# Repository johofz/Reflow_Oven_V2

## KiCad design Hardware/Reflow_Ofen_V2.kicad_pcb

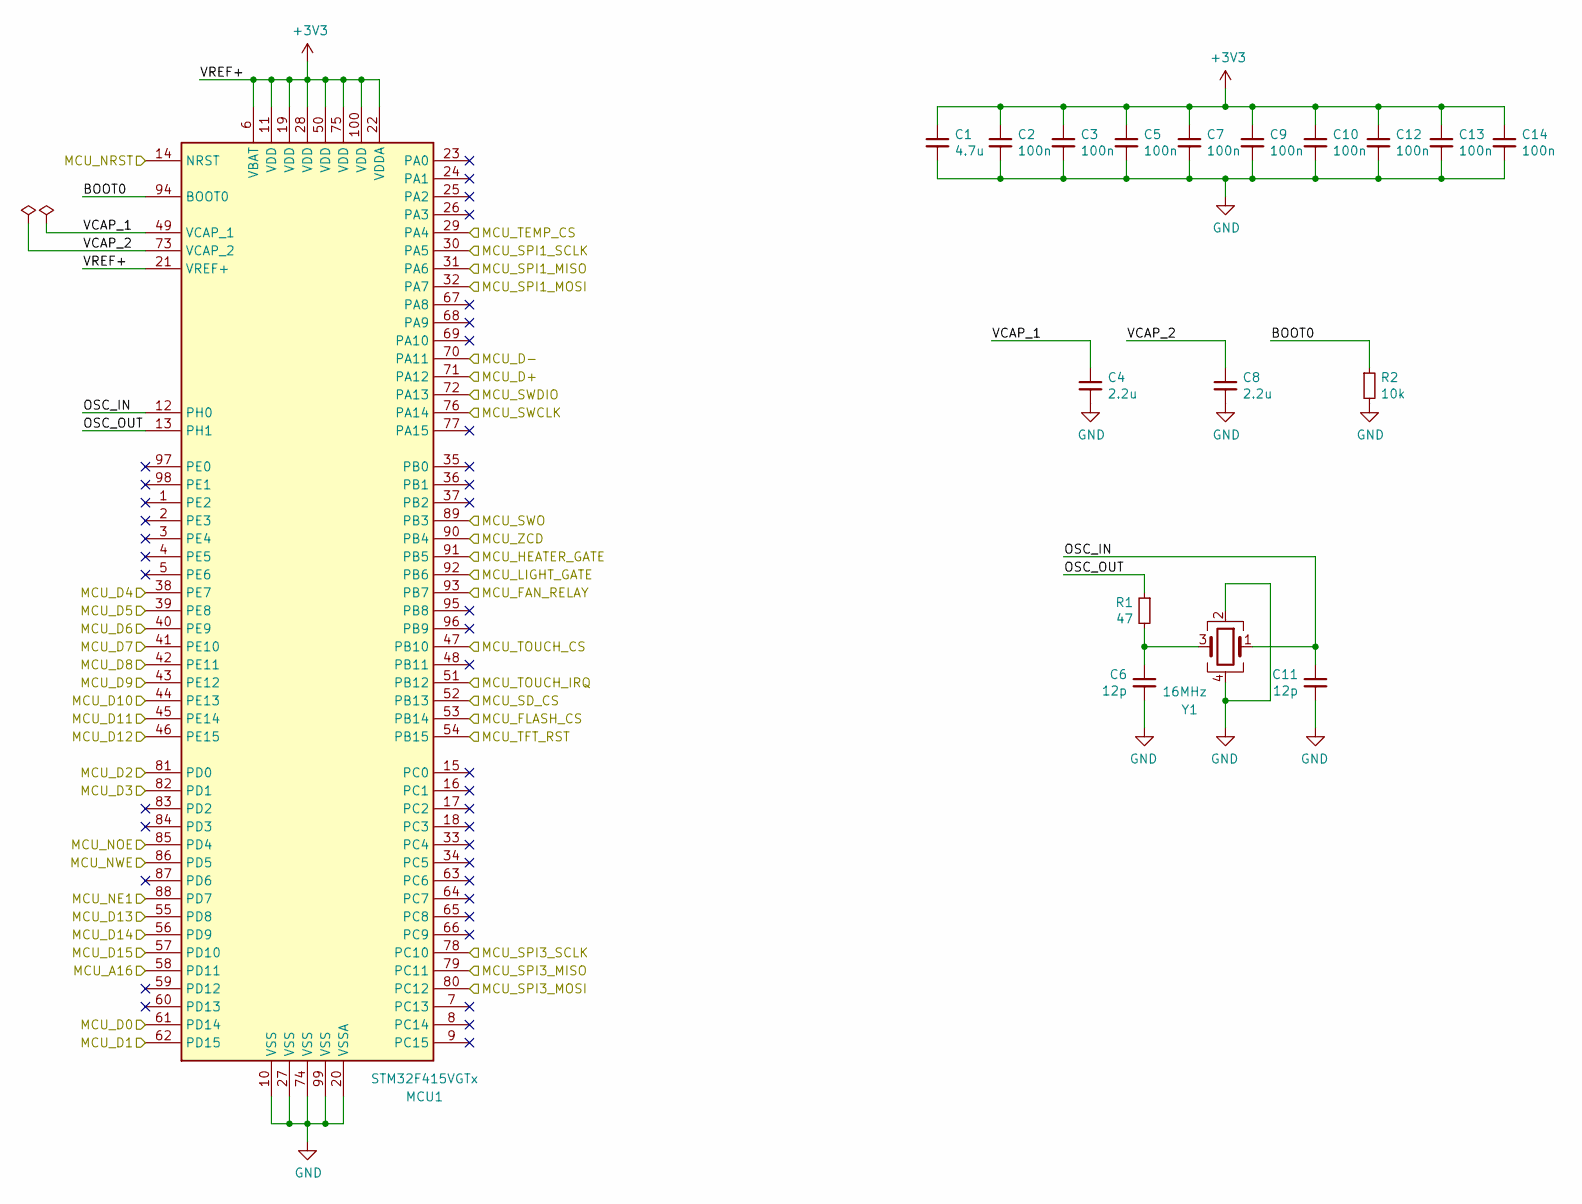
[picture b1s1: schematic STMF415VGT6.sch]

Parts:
C1: 4.7u; C_0603_1608Metric; LCSC C19666
C2, C3, C5, C7, C9, C10, C12, C13, C14: 100n; C_0402_1005Metric; LCSC C1525
C4, C8: 2.2u; C_0603_1608Metric; LCSC C23630
C6, C11: 12p; C_0402_1005Metric; LCSC C1547
MCU1: STM32F415VGTx; LQFP-100_14x14mm_P0.5mm; LCSC C118210
R1: 47; R_0402_1005Metric; LCSC C25118
R2: 10k; R_0402_1005Metric; LCSC C25744
Y1: 16MHz; Crystal_SMD_3225-4Pin_3.2x2.5mm; LCSC C13738

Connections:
/Connectors/CONN_D+: MCU1.71 (PA12); also elsewhere on the board
/Connectors/CONN_D-: MCU1.70 (PA11); also elsewhere on the board
/Connectors/CONN_NRST: MCU1.14 (NRST); also elsewhere on the board
/Connectors/CONN_SWCLK: MCU1.76 (PA14); also elsewhere on the board
/Connectors/CONN_SWDIO: MCU1.72 (PA13); also elsewhere on the board
/Connectors/CONN_SWO: MCU1.89 (PB3); also elsewhere on the board
/FLASH_CS: MCU1.53 (PB14); also elsewhere on the board
/Power-Control/FAN_GATE: MCU1.93 (PB7); also elsewhere on the board
/Power-Control/HEATER_GATE: MCU1.91 (PB5); also elsewhere on the board
/Power-Control/LIGHT_GATE: MCU1.92 (PB6); also elsewhere on the board
/SD_CS: MCU1.52 (PB13); also elsewhere on the board
/SPI3_MISO: MCU1.79 (PC11); also elsewhere on the board
/SPI3_MOSI: MCU1.80 (PC12); also elsewhere on the board
/SPI3_SCLK: MCU1.78 (PC10); also elsewhere on the board
/STMF415VGT6/BOOT0: MCU1.94 (BOOT0), R2.1
/STMF415VGT6/MCU_A16: MCU1.58 (PD11); also elsewhere on the board
/STMF415VGT6/MCU_D0: MCU1.61 (PD14); also elsewhere on the board
/STMF415VGT6/MCU_D1: MCU1.62 (PD15); also elsewhere on the board
/STMF415VGT6/MCU_D2: MCU1.81 (PD0); also elsewhere on the board
/STMF415VGT6/MCU_D3: MCU1.82 (PD1); also elsewhere on the board
/STMF415VGT6/MCU_D4: MCU1.38 (PE7); also elsewhere on the board
/STMF415VGT6/MCU_D5: MCU1.39 (PE8); also elsewhere on the board
/STMF415VGT6/MCU_D6: MCU1.40 (PE9); also elsewhere on the board
/STMF415VGT6/MCU_D7: MCU1.41 (PE10); also elsewhere on the board
/STMF415VGT6/MCU_D8: MCU1.42 (PE11); also elsewhere on the board
/STMF415VGT6/MCU_D9: MCU1.43 (PE12); also elsewhere on the board
/STMF415VGT6/MCU_D10: MCU1.44 (PE13); also elsewhere on the board
/STMF415VGT6/MCU_D11: MCU1.45 (PE14); also elsewhere on the board
/STMF415VGT6/MCU_D12: MCU1.46 (PE15); also elsewhere on the board
/STMF415VGT6/MCU_D13: MCU1.55 (PD8); also elsewhere on the board
/STMF415VGT6/MCU_D14: MCU1.56 (PD9); also elsewhere on the board
/STMF415VGT6/MCU_D15: MCU1.57 (PD10); also elsewhere on the board
/STMF415VGT6/MCU_NE1: MCU1.88 (PD7); also elsewhere on the board
/STMF415VGT6/MCU_NOE: MCU1.85 (PD4); also elsewhere on the board
/STMF415VGT6/MCU_NWE: MCU1.86 (PD5); also elsewhere on the board
/STMF415VGT6/MCU_SPI1_MISO: MCU1.31 (PA6); also elsewhere on the board
/STMF415VGT6/MCU_SPI1_SCLK: MCU1.30 (PA5); also elsewhere on the board
/STMF415VGT6/MCU_TEMP_CS: MCU1.29 (PA4); also elsewhere on the board
/STMF415VGT6/MCU_TFT_RST: MCU1.54 (PB15); also elsewhere on the board
/STMF415VGT6/MCU_ZCD: MCU1.90 (PB4); also elsewhere on the board
/STMF415VGT6/OSC_IN: C11.1, MCU1.12 (PH0), Y1.1
/STMF415VGT6/OSC_OUT: MCU1.13 (PH1), R1.1
/STMF415VGT6/VCAP_1: C4.1, MCU1.49 (VCAP_1)
/STMF415VGT6/VCAP_2: C8.1, MCU1.73 (VCAP_2)
/TOUCH_CS: MCU1.47 (PB10); also elsewhere on the board
/TOUCH_IRQ: MCU1.51 (PB12); also elsewhere on the board
GND: C1.2, C2.2, C3.2, C4.2, C5.2, C6.2, C7.2, C8.2, C9.2, C10.2, C11.2, C12.2, C13.2, C14.2, MCU1.10 (VSS), MCU1.20 (VSSA), MCU1.27 (VSS), MCU1.74 (VSS), MCU1.99 (VSS), R2.2, Y1.2, Y1.4; also elsewhere on the board
unnamed: C6.1, R1.2, Y1.3

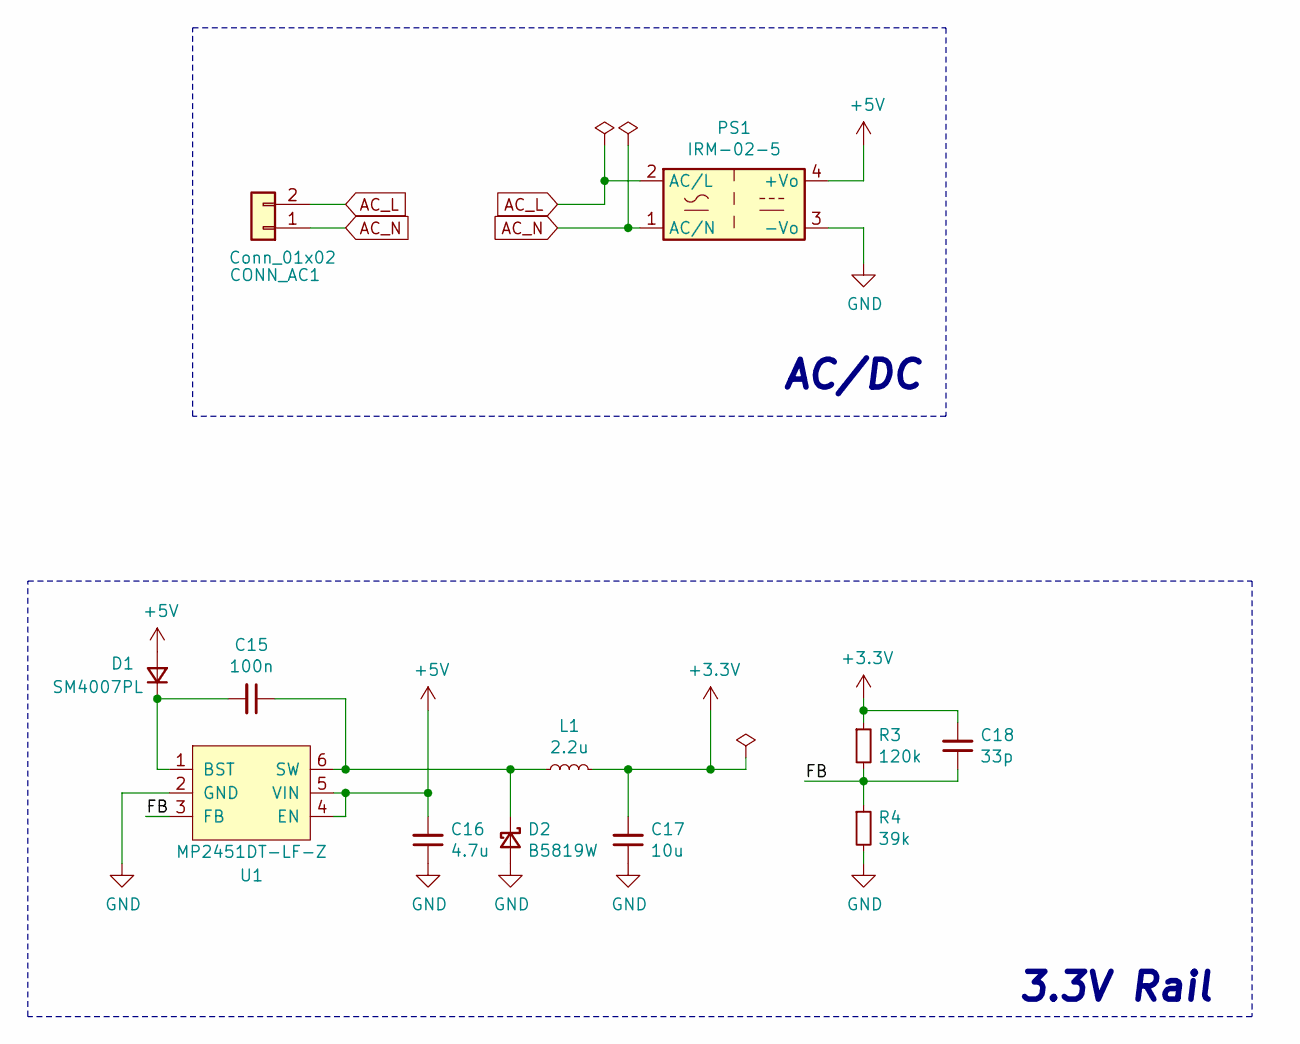
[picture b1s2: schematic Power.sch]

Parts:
C15: 100n; C_0402_1005Metric; LCSC C1525
C16: 4.7u; C_0805_2012Metric; LCSC C1779
C17: 10u; C_0805_2012Metric; LCSC C15850
C18: 33p; C_0603_1608Metric; LCSC C1663
CONN_AC1: Conn_01x02; TerminalBlock_Wuerth_691311400102_P7.62mm; LCSC C8422
D1: SM4007PL; D_SOD-123F; LCSC C64898
D2: B5819W; D_SOD-123; LCSC C8598
L1: 2.2u; L_Sunlord_MWSA0518_5.4x5.2mm; LCSC C408345
PS1: IRM-02-5; Converter_ACDC_MeanWell_IRM-02-xx_THT
R3: 120k; R_0805_2012Metric; LCSC C17436
R4: 39k; R_0805_2012Metric; LCSC C25826
U1: MP2451DT-LF-Z; TSOT-23-6; LCSC C85285

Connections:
+5V: C16.2, D1.2 (A), PS1.4 (+Vo), U1.4 (EN), U1.5 (VIN); also elsewhere on the board
/Power/FB: C18.1, R3.2, R4.1, U1.3 (FB)
AC_L: CONN_AC1.2, PS1.2 (AC/L); also elsewhere on the board
AC_N: CONN_AC1.1, PS1.1 (AC/N); also elsewhere on the board
GND: C16.1, C17.1, D2.2 (A), PS1.3 (-Vo), R4.2, U1.2 (GND); also elsewhere on the board
unnamed: C15.1, D2.1 (K), L1.1, U1.6 (SW)
unnamed: C15.2, D1.1 (K), U1.1 (BST)

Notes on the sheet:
3.3V Rail
AC/DC

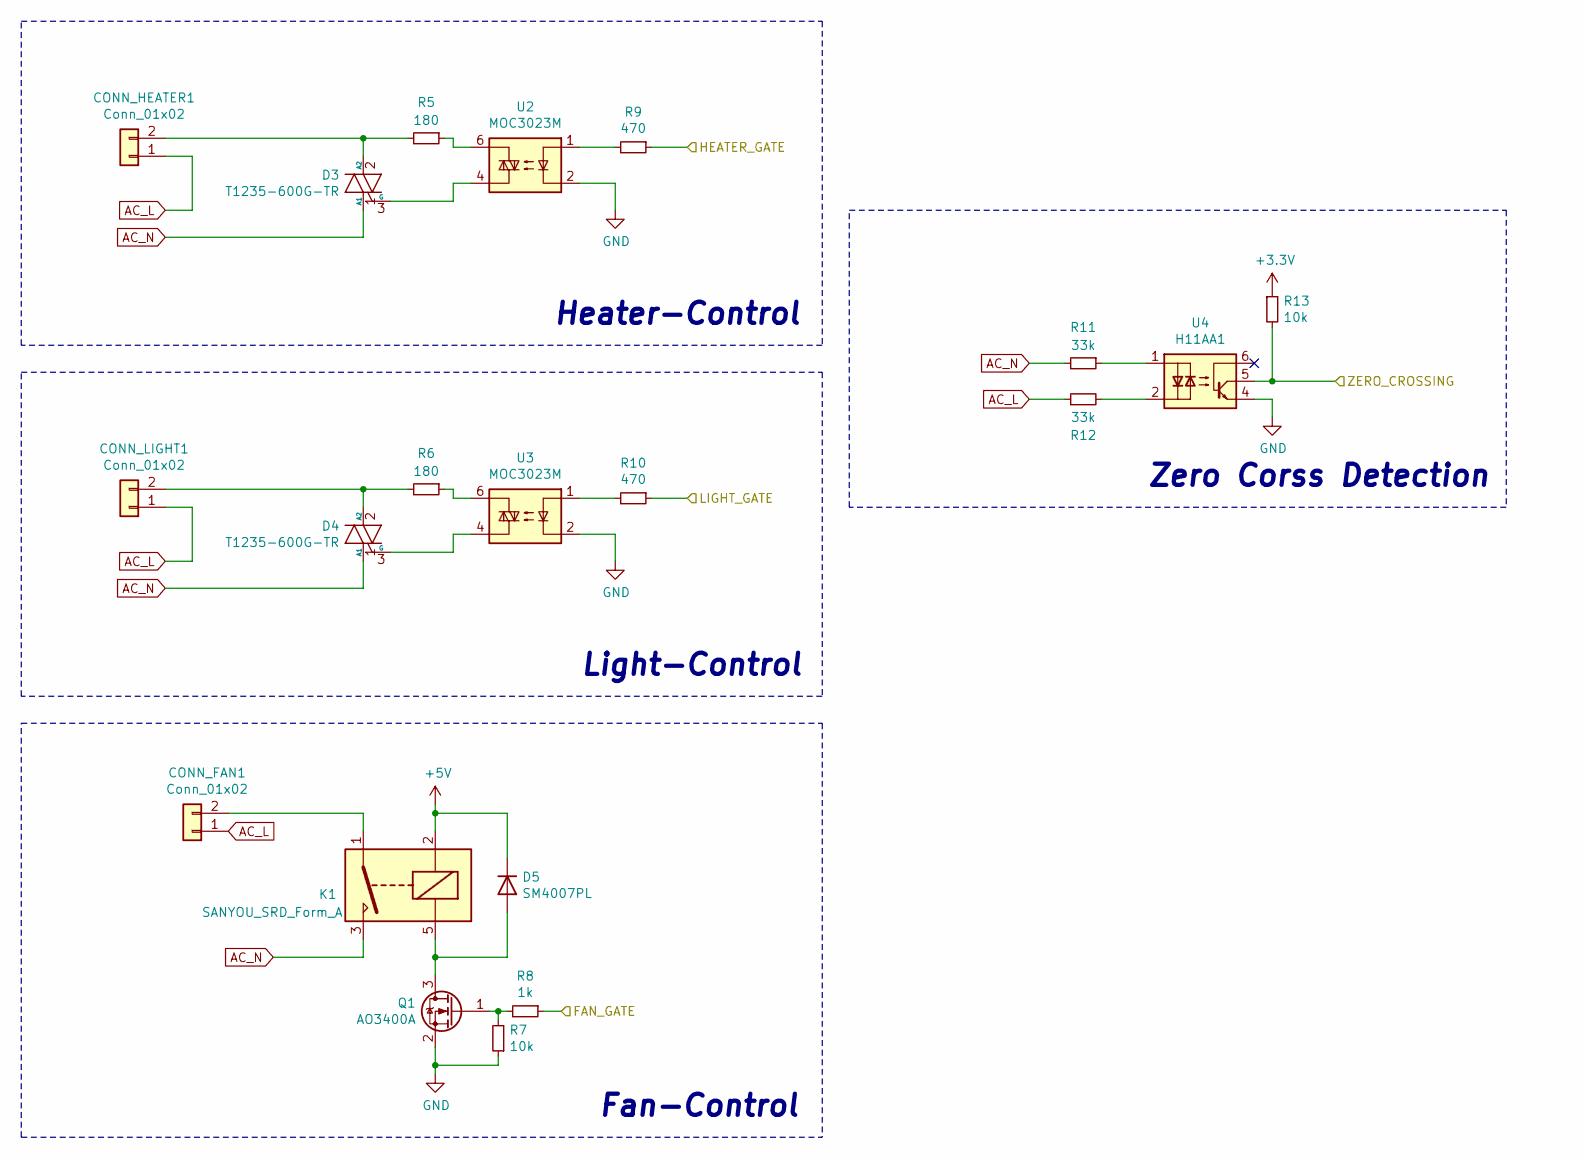
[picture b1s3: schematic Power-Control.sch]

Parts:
CONN_FAN1: Conn_01x02; TerminalBlock_Wuerth_691311400102_P7.62mm; LCSC C8422
CONN_HEATER1: Conn_01x02; TerminalBlock_Wuerth_691311400102_P7.62mm; LCSC C8422
CONN_LIGHT1: Conn_01x02; TerminalBlock_Wuerth_691311400102_P7.62mm; LCSC C8422
D3: T1235-600G-TR; TO-220-3_Vertical
D4: T1235-600G-TR; TO-263-2; LCSC C155555
D5: SM4007PL; D_SOD-123F; LCSC C64898
K1: SANYOU_SRD_Form_A; Relay_SPST_SANYOU_SRD_Series_Form_A; LCSC C35449
Q1: AO3400A; SOT-23; LCSC C20917
R5, R6: 180; R_0805_2012Metric; LCSC C25270
R7, R13: 10k; R_0603_1608Metric; LCSC C25804
R8: 1k; R_0603_1608Metric; LCSC C21190
R9, R10: 470; R_0603_1608Metric; LCSC C25117
R11, R12: 33k; R_0805_2012Metric; LCSC C17633
U2, U3: MOC3023M; SMDIP-6_W9.53mm; LCSC C40701
U4: H11AA1; SMDIP-6_W9.53mm; LCSC C258253

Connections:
+5V: D5.1 (K), K1.2; also elsewhere on the board
/Power-Control/FAN_GATE: R8.1; also elsewhere on the board
/Power-Control/HEATER_GATE: R9.1; also elsewhere on the board
/Power-Control/LIGHT_GATE: R10.1; also elsewhere on the board
/STMF415VGT6/MCU_ZCD: R13.2, U4.5; also elsewhere on the board
AC_L: CONN_FAN1.1, CONN_HEATER1.1, CONN_LIGHT1.1, R12.1; also elsewhere on the board
AC_N: D3.1 (A1), D4.1 (A1), K1.3, R11.2; also elsewhere on the board
GND: Q1.2 (S), R7.1, U2.2, U3.2, U4.4; also elsewhere on the board
unnamed: CONN_FAN1.2, K1.1
unnamed: CONN_HEATER1.2, D3.2 (A2), R5.2
unnamed: CONN_LIGHT1.2, D4.2 (A2), R6.2
unnamed: D3.3 (G), U2.4
unnamed: D4.3 (G), U3.4
unnamed: D5.2 (A), K1.5, Q1.3 (D)
unnamed: Q1.1 (G), R7.2, R8.2
unnamed: R5.1, U2.6
unnamed: R6.1, U3.6
unnamed: R9.2, U2.1
unnamed: R10.2, U3.1
unnamed: R11.1, U4.1
unnamed: R12.2, U4.2

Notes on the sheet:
Heater-Control
Zero Corss Detection
Light-Control
Fan-Control

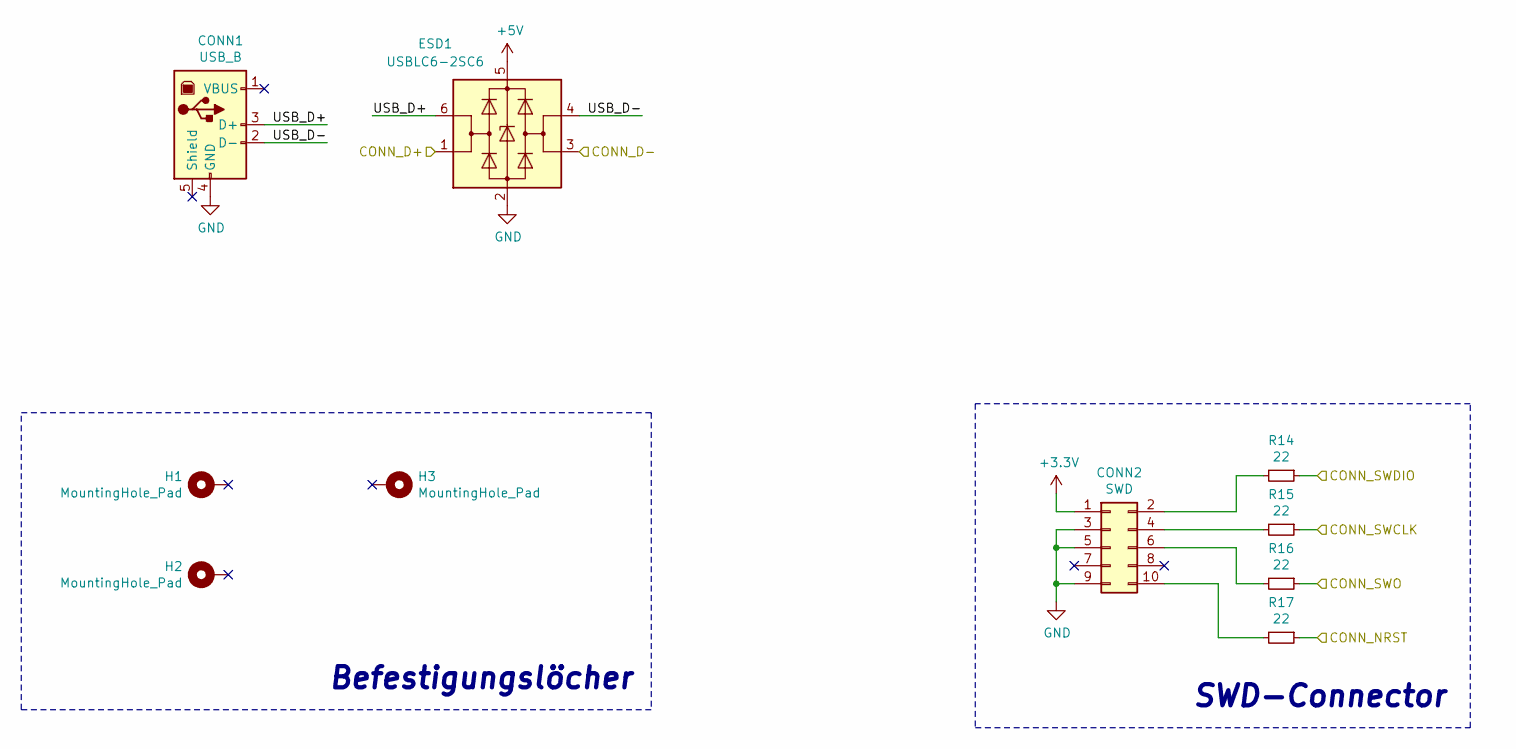
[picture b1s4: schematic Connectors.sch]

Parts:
CONN1: USB_B; USB_B_OST_USB-B1HSxx_Horizontal
CONN2: SWD; PinHeader_2x05_P1.27mm_Vertical_SMD
ESD1: USBLC6-2SC6; SOT-23-6; LCSC C7519
H1, H2, H3: MountingHole_Pad; MountingHole_5.3mm_M5_Pad_Via
R14, R15, R16, R17: 22; R_0402_1005Metric; LCSC C25092

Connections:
+5V: ESD1.5 (VBUS); also elsewhere on the board
/Connectors/CONN_D+: ESD1.1 (I/O1); also elsewhere on the board
/Connectors/CONN_D-: ESD1.3 (I/O2); also elsewhere on the board
/Connectors/CONN_NRST: R17.1; also elsewhere on the board
/Connectors/CONN_SWCLK: R15.1; also elsewhere on the board
/Connectors/CONN_SWDIO: R14.1; also elsewhere on the board
/Connectors/CONN_SWO: R16.1; also elsewhere on the board
/Connectors/USB_D+: CONN1.3 (D+), ESD1.6 (I/O1)
/Connectors/USB_D-: CONN1.2 (D-), ESD1.4 (I/O2)
GND: CONN1.4 (GND), CONN2.3, CONN2.5, CONN2.9, ESD1.2 (GND); also elsewhere on the board
unnamed: CONN2.2, R14.2
unnamed: CONN2.4, R15.2
unnamed: CONN2.6, R16.2
unnamed: CONN2.10, R17.2

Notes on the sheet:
SWD-Connector
Befestigungslöcher

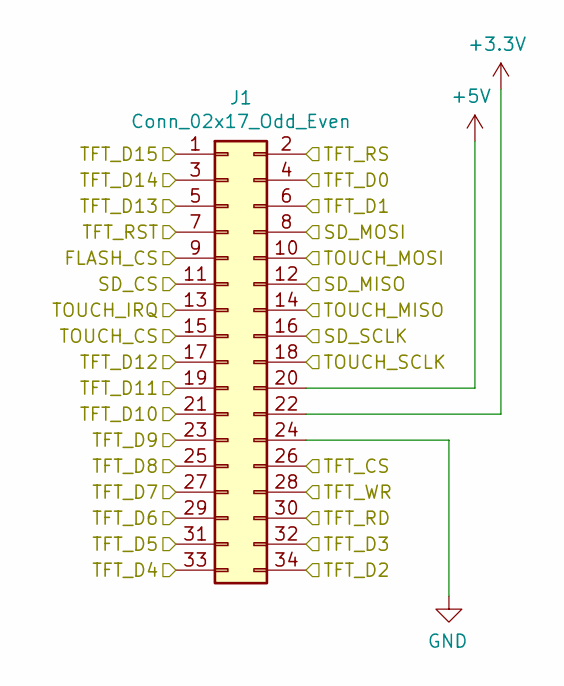
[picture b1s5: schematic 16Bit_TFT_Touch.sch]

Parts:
J1: Conn_02x17_Odd_Even; PinHeader_2x17_P1.27mm_Vertical

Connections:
+5V: J1.20; also elsewhere on the board
/FLASH_CS: J1.9; also elsewhere on the board
/SD_CS: J1.11; also elsewhere on the board
/SPI3_MISO: J1.12, J1.14; also elsewhere on the board
/SPI3_MOSI: J1.8, J1.10; also elsewhere on the board
/SPI3_SCLK: J1.16, J1.18; also elsewhere on the board
/STMF415VGT6/MCU_A16: J1.2; also elsewhere on the board
/STMF415VGT6/MCU_D0: J1.4; also elsewhere on the board
/STMF415VGT6/MCU_D1: J1.6; also elsewhere on the board
/STMF415VGT6/MCU_D2: J1.34; also elsewhere on the board
/STMF415VGT6/MCU_D3: J1.32; also elsewhere on the board
/STMF415VGT6/MCU_D4: J1.33; also elsewhere on the board
/STMF415VGT6/MCU_D5: J1.31; also elsewhere on the board
/STMF415VGT6/MCU_D6: J1.29; also elsewhere on the board
/STMF415VGT6/MCU_D7: J1.27; also elsewhere on the board
/STMF415VGT6/MCU_D8: J1.25; also elsewhere on the board
/STMF415VGT6/MCU_D9: J1.23; also elsewhere on the board
/STMF415VGT6/MCU_D10: J1.21; also elsewhere on the board
/STMF415VGT6/MCU_D11: J1.19; also elsewhere on the board
/STMF415VGT6/MCU_D12: J1.17; also elsewhere on the board
/STMF415VGT6/MCU_D13: J1.5; also elsewhere on the board
/STMF415VGT6/MCU_D14: J1.3; also elsewhere on the board
/STMF415VGT6/MCU_D15: J1.1; also elsewhere on the board
/STMF415VGT6/MCU_NE1: J1.26; also elsewhere on the board
/STMF415VGT6/MCU_NOE: J1.30; also elsewhere on the board
/STMF415VGT6/MCU_NWE: J1.28; also elsewhere on the board
/STMF415VGT6/MCU_TFT_RST: J1.7; also elsewhere on the board
/TOUCH_CS: J1.15; also elsewhere on the board
/TOUCH_IRQ: J1.13; also elsewhere on the board
GND: J1.24; also elsewhere on the board

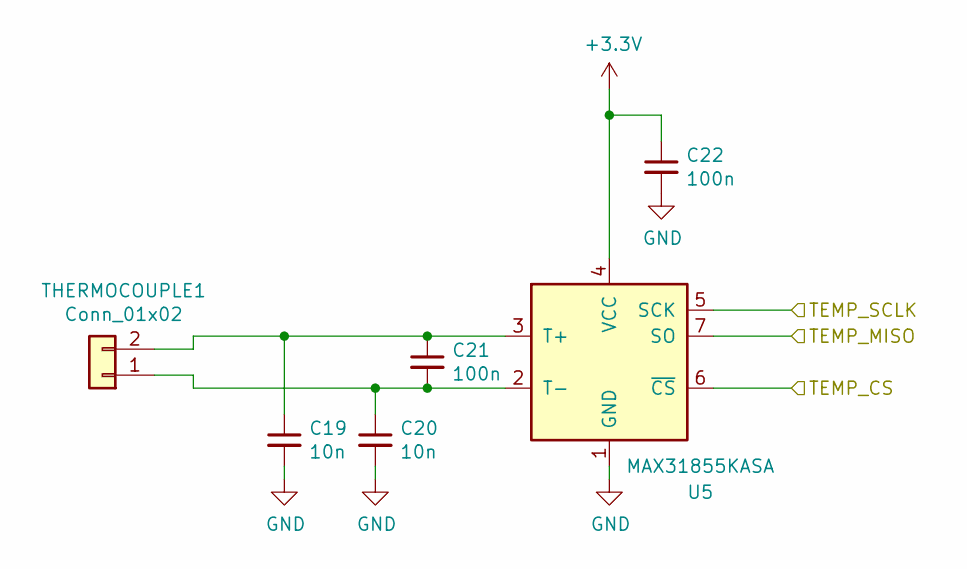
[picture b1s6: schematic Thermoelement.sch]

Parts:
C19, C20: 10n; C_0402_1005Metric; LCSC C15195
C21, C22: 100n; C_0402_1005Metric; LCSC C1525
THERMOCOUPLE1: Conn_01x02; TerminalBlock_bornier-2_P5.08mm; LCSC C395868
U5: MAX31855KASA; SOIC-8_3.9x4.9mm_P1.27mm; LCSC C52028

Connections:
/STMF415VGT6/MCU_SPI1_MISO: U5.7 (SO); also elsewhere on the board
/STMF415VGT6/MCU_SPI1_SCLK: U5.5 (SCK); also elsewhere on the board
/STMF415VGT6/MCU_TEMP_CS: U5.6 (~CS~); also elsewhere on the board
GND: C19.2, C20.2, C22.2, U5.1 (GND); also elsewhere on the board
unnamed: C19.1, C21.1, THERMOCOUPLE1.2, U5.3 (T+)
unnamed: C20.1, C21.2, THERMOCOUPLE1.1, U5.2 (T-)

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
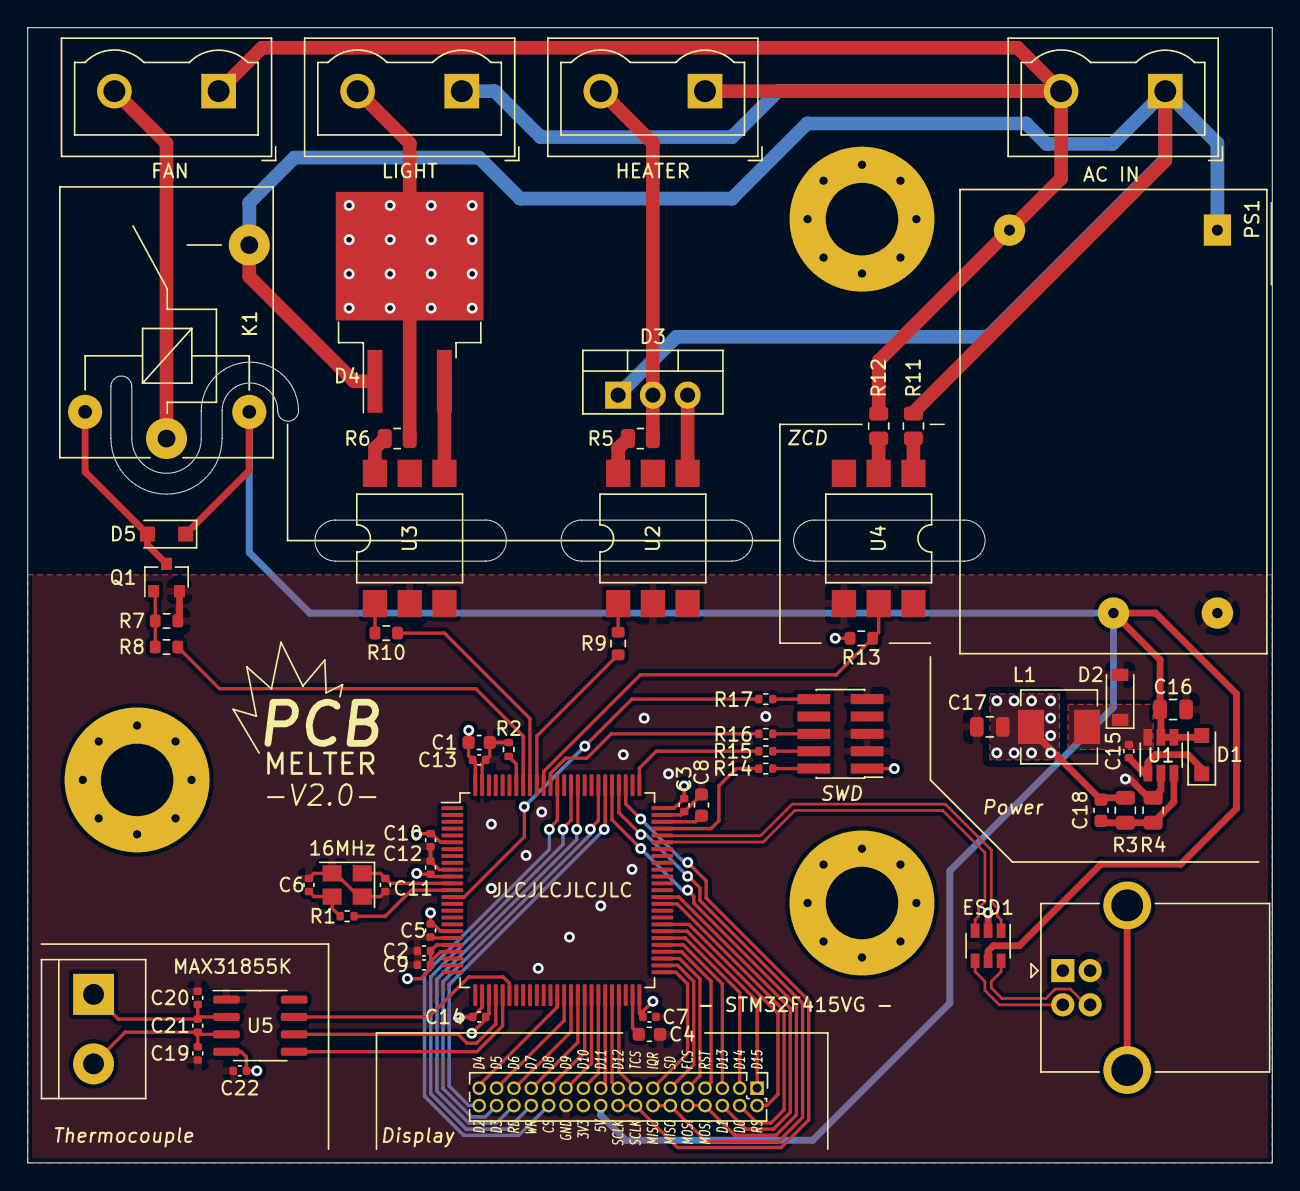
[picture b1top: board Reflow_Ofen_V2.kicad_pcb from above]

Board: 4 copper layers, 91.0 x 83.0 mm, 67 parts (0 on the bottom side), 76 nets.

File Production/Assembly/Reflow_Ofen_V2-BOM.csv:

Comment,Designator,Footprint,LCSC
"4.7u","C1","Capacitor_SMD:C_0603_1608Metric","C19666"
"12p","C6,C11","Capacitor_SMD:C_0402_1005Metric","C1547"
"4.7u","C16","Capacitor_SMD:C_0805_2012Metric","C1779"
"10u","C17","Capacitor_SMD:C_0805_2012Metric","C15850"
"33p","C18","Capacitor_SMD:C_0603_1608Metric","C1663"
"100n","C2,C3,C5,C7,C9,C10,C12,C13,C14,C15,C21,C22","Capacitor_SMD:C_0402_1005Metric","C1525"
"10n","C19,C20","Capacitor_SMD:C_0402_1005Metric","C15195"
"2.2u","C4,C8","Capacitor_SMD:C_0603_1608Metric","C23630"
"USB_B","CONN1","Connector_USB:USB_B_OST_USB-B1HSxx_Horizontal",""
"SWD","CONN2","Connector_PinHeader_1.27mm:PinHeader_2x05_P1.27mm_Vertical_SMD",""
"Conn_01x02","CONN_AC1,CONN_HEATER1,CONN_LIGHT1,CONN_FAN1","TerminalBlock:TerminalBlock_Wuerth_691311400102_P7.62mm","C8422"
"SM4007PL","D1,D5","Diode_SMD:D_SOD-123F","C64898"
"B5819W","D2","Diode_SMD:D_SOD-123","C8598"
"T1235-600G-TR","D3","Package_TO_SOT_THT:TO-220-3_Vertical",""
"T1235-600G-TR","D4","Package_TO_SOT_SMD:TO-263-2","C155555"
"USBLC6-2SC6","ESD1","Package_TO_SOT_SMD:SOT-23-6","C7519"
"MountingHole_Pad","H1,H2,H3","MountingHole:MountingHole_5.3mm_M5_Pad_Via",""
"Conn_02x17_Odd_Even","J1","Connector_PinHeader_1.27mm:PinHeader_2x17_P1.27mm_Vertical",""
"SANYOU_SRD_Form_A","K1","Relay_THT:Relay_SPST_SANYOU_SRD_Series_Form_A","C35449"
"2.2u","L1","Inductor_SMD:L_Sunlord_MWSA0518_5.4x5.2mm","C408345"
"STM32F415VGTx","MCU1","Package_QFP:LQFP-100_14x14mm_P0.5mm","C118210"
"IRM-02-5","PS1","Converter_ACDC:Converter_ACDC_MeanWell_IRM-02-xx_THT",""
"AO3400A","Q1","Package_TO_SOT_SMD:SOT-23","C20917"
"47","R1","Resistor_SMD:R_0402_1005Metric","C25118"
"33k","R11,R12","Resistor_SMD:R_0805_2012Metric","C17633"
"10k","R7,R13","Resistor_SMD:R_0603_1608Metric","C25804"
"22","R14,R15,R16,R17","Resistor_SMD:R_0402_1005Metric","C25092"
"10k","R2","Resistor_SMD:R_0402_1005Metric","C25744"
"120k","R3","Resistor_SMD:R_0805_2012Metric","C17436"
"39k","R4","Resistor_SMD:R_0805_2012Metric","C25826"
"180","R5,R6","Resistor_SMD:R_0805_2012Metric","C25270"
"1k","R8","Resistor_SMD:R_0603_1608Metric","C21190"
"470","R9,R10","Resistor_SMD:R_0603_1608Metric","C25117"
"Conn_01x02","THERMOCOUPLE1","TerminalBlock:TerminalBlock_bornier-2_P5.08mm","C395868"
"MP2451DT-LF-Z","U1","Package_TO_SOT_SMD:TSOT-23-6","C85285"
"MOC3023M","U2,U3","Package_DIP:SMDIP-6_W9.53mm","C40701"
"H11AA1","U4","Package_DIP:SMDIP-6_W9.53mm","C258253"
"MAX31855KASA","U5","Package_SO:SOIC-8_3.9x4.9mm_P1.27mm","C52028"
"16MHz","Y1","Crystal:Crystal_SMD_3225-4Pin_3.2x2.5mm","C13738"

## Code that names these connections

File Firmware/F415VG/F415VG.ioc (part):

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PD7.Mode=NorPsramChipSelect1_1
PB13.GPIOParameters=GPIO_Label
PA6.Mode=Full_Duplex_Master
PH0-OSC_IN.Signal=RCC_OSC_IN
Mcu.UserName=STM32F415VGTx
PB4.GPIO_ModeDefaultEXTI=GPIO_MODE_IT_FALLING
PC10.Signal=SPI3_SCK
PC12.Signal=SPI3_MOSI
PB14.GPIO_Label=SD_CS
PA11.Mode=Device_Only
PB6.GPIO_Label=LIGHT
PB13.GPIO_Label=FLASH_CS
PB13.Signal=GPIO_Output
PB15.Signal=GPIO_Output
PD9.Mode=16b-d1
RCC.SYSCLKSource=RCC_SYSCLKSOURCE_PLLCLK
PB5.GPIOParameters=GPIO_Label
PB4.GPIOParameters=GPIO_Label,GPIO_ModeDefaultEXTI
PA12.Signal=USB_OTG_FS_DP
PE11.Mode=16b-d1
PD4.Signal=FSMC_NOE
PB6.Signal=GPIO_Output
PD10.Mode=16b-d1
PD0.Signal=FSMC_D2
PD8.Signal=FSMC_D13
PH0-OSC_IN.Mode=HSE-External-Oscillator
PD5.Mode=Lcd1
RCC.HSE_VALUE=16000000
PB3.Mode=Trace_Asynchronous_SW
PB12.GPIO_Label=TOUCH_IQR
PE13.Signal=FSMC_D10
PE9.Signal=FSMC_D6
PA14.Mode=Trace_Asynchronous_SW
PD14.Mode=16b-d1
PB7.Signal=GPIO_Output
PE13.Mode=16b-d1
PE10.Signal=FSMC_D7
PB6.GPIOParameters=GPIO_Label
PD15.Mode=16b-d1
PH1-OSC_OUT.Mode=HSE-External-Oscillator
PB7.GPIO_Label=FAN
Mcu.Package=LQFP100
PA6.Signal=SPI1_MISO
PE9.Mode=16b-d1
PC11.Mode=Full_Duplex_Master
PB14.GPIOParameters=GPIO_Label
PB5.GPIO_Label=HEATER
PD4.Mode=Lcd1
PB10.GPIOParameters=GPIO_Label
PE7.Signal=FSMC_D4
PA4.GPIO_Label=TEMP_CS
PD15.Signal=FSMC_D1
PB4.Signal=GPXTI4
PA5.Mode=Full_Duplex_Master
PE12.Mode=16b-d1
PA7.Mode=Full_Duplex_Master
PC11.Signal=SPI3_MISO
PE10.Mode=16b-d1
PC10.Mode=Full_Duplex_Master
PD7.Signal=FSMC_NE1
PD1.Signal=FSMC_D3
PD5.Signal=FSMC_NWE
PD9.Signal=FSMC_D14
PE8.Mode=16b-d1
PD10.Signal=FSMC_D15
PA13.Signal=SYS_JTMS-SWDIO
PB10.GPIO_Label=TOUCH_CS
PB7.GPIOParameters=GPIO_Label
PE11.Signal=FSMC_D8
PD8.Mode=16b-d1
PB10.Signal=GPIO_Output
PB14.Signal=GPIO_Output
PA5.Signal=SPI1_SCK
PC12.Mode=Full_Duplex_Master
board=custom
PD1.Mode=16b-d1
PE14.Signal=FSMC_D11
PE15.Signal=FSMC_D12
PB4.GPIO_Label=ZCD
PB15.GPIO_Label=TFT_RST
PE8.Signal=FSMC_D5
PE14.Mode=16b-d1
PH1-OSC_OUT.Signal=RCC_OSC_OUT
PA4.GPIOParameters=GPIO_Label
PB15.GPIOParameters=GPIO_Label
PA13.Mode=Trace_Asynchronous_SW
Mcu.Name=STM32F415VGTx
PD0.Mode=16b-d1
PE12.Signal=FSMC_D9
PD14.Signal=FSMC_D0
PB3.Signal=SYS_JTDO-SWO
PA4.Signal=GPIO_Output
RCC.SYSCLKFreq_VALUE=168000000
PE7.Mode=16b-d1
PB5.Signal=GPIO_Output
PA12.Mode=Device_Only
PD11.Signal=FSMC_A16
PA11.Signal=USB_OTG_FS_DM
PA14.Signal=SYS_JTCK-SWCLK
PD11.Mode=A16_1
PB12.GPIOParameters=GPIO_Label
PB12.Signal=GPXTI12
PE15.Mode=16b-d1
PA7.Signal=SPI1_MOSI

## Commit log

2021-04-21 Funktionalität für Verbraucher hinzugefügt. PID-Controller hinzugefügt. MAX31855 Driver hinzugefügt. Minimalbeispiel für Reflow-Prozess erstellt.
2021-04-26 Setup-Code für FSMC.
